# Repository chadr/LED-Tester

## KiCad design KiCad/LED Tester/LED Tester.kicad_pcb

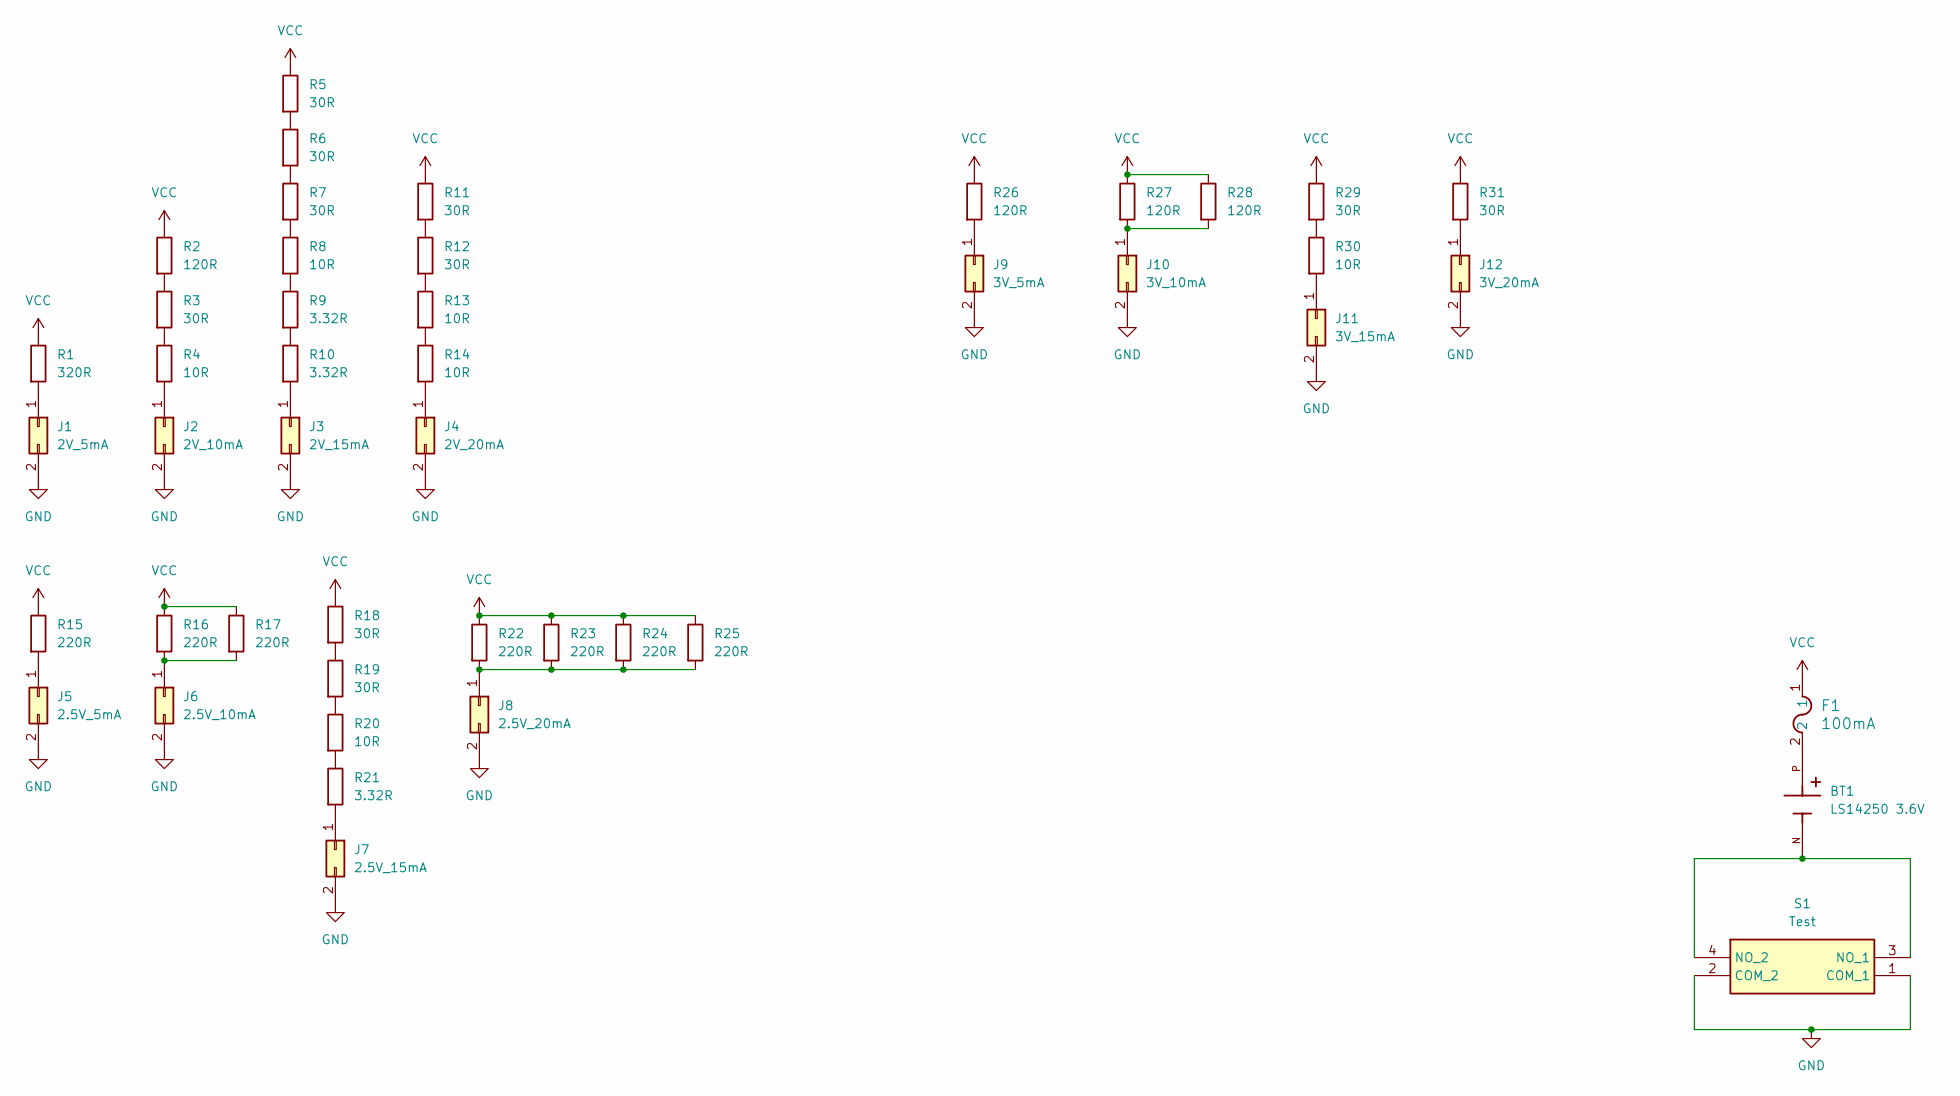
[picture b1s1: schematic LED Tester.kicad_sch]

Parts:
BT1: LS14250 3.6V; BAT_108; PARTREV E
F1: 100mA; FUSE_0PTF0078P_LTF
J1: 2V_5mA; PinHeader_2x01_P2.54mm_Vertical
J2: 2V_10mA; PinHeader_2x01_P2.54mm_Vertical
J3: 2V_15mA; PinHeader_2x01_P2.54mm_Vertical
J4: 2V_20mA; PinHeader_2x01_P2.54mm_Vertical
J5: 2.5V_5mA; PinHeader_2x01_P2.54mm_Vertical
J6: 2.5V_10mA; PinHeader_2x01_P2.54mm_Vertical
J7: 2.5V_15mA; PinHeader_2x01_P2.54mm_Vertical
J8: 2.5V_20mA; PinHeader_2x01_P2.54mm_Vertical
J9: 3V_5mA; PinHeader_2x01_P2.54mm_Vertical
J10: 3V_10mA; PinHeader_2x01_P2.54mm_Vertical
J11: 3V_15mA; PinHeader_2x01_P2.54mm_Vertical
J12: 3V_20mA; PinHeader_2x01_P2.54mm_Vertical
R1: 320R; R_1206_3216Metric
R2, R26, R27, R28: 120R; R_1206_3216Metric
R3, R5, R6, R7, R11, R12, R18, R19, R29, R31: 30R; R_1206_3216Metric
R4, R8, R13, R14, R20, R30: 10R; R_1206_3216Metric
R9, R10, R21: 3.32R; R_1206_3216Metric
R15, R16, R17, R22, R23, R24, R25: 220R; R_1206_3216Metric
S1: Test; FSM6JH; Manufacturer_Part_Number FSM6JH; Mouser Part Number 506-FSM6JH

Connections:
GND: J1.2, J2.2, J3.2, J4.2, J5.2, J6.2, J7.2, J8.2, J9.2, J10.2, J11.2, J12.2, S1.1 (COM_1), S1.2 (COM_2)
unnamed: BT1.P, F1.2
unnamed: J1.1, R1.2
unnamed: J2.1, R4.2
unnamed: J3.1, R10.2
unnamed: J4.1, R14.2
unnamed: J5.1, R15.2
unnamed: J6.1, R16.2, R17.2
unnamed: J7.1, R21.2
unnamed: J8.1, R22.2, R23.2, R24.2, R25.2
unnamed: J9.1, R26.2
unnamed: J10.1, R27.2, R28.2
unnamed: J11.1, R30.2
unnamed: J12.1, R31.2
unnamed: R2.2, R3.1
unnamed: R3.2, R4.1
unnamed: R5.2, R6.1
unnamed: R6.2, R7.1
unnamed: R7.2, R8.1
unnamed: R8.2, R9.1
unnamed: R9.2, R10.1
unnamed: R11.2, R12.1
unnamed: R12.2, R13.1
unnamed: R13.2, R14.1
unnamed: R18.2, R19.1
unnamed: R19.2, R20.1
unnamed: R20.2, R21.1
unnamed: R29.2, R30.1
unnamed: BT1.N, S1.3 (NO_1), S1.4 (NO_2)
VCC: F1.1, R1.1, R2.1, R5.1, R11.1, R15.1, R16.1, R17.1, R18.1, R22.1, R23.1, R24.1, R25.1, R26.1, R27.1, R28.1, R29.1, R31.1

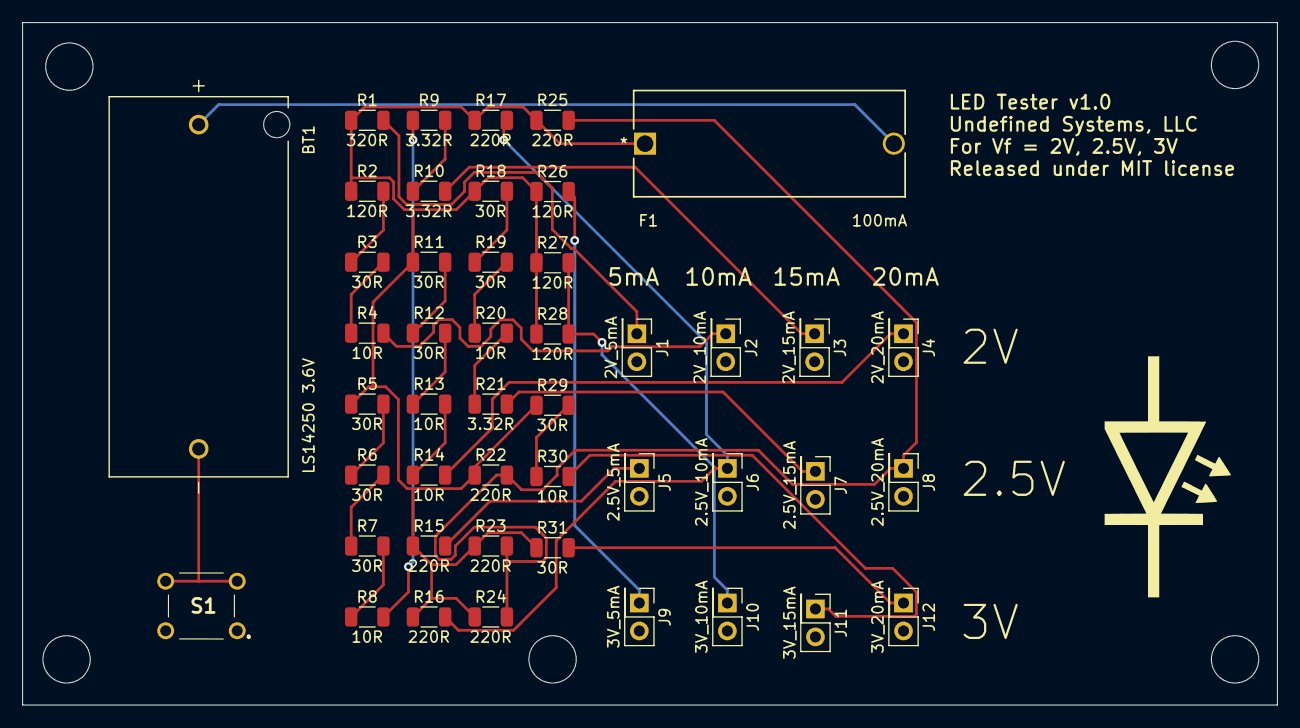
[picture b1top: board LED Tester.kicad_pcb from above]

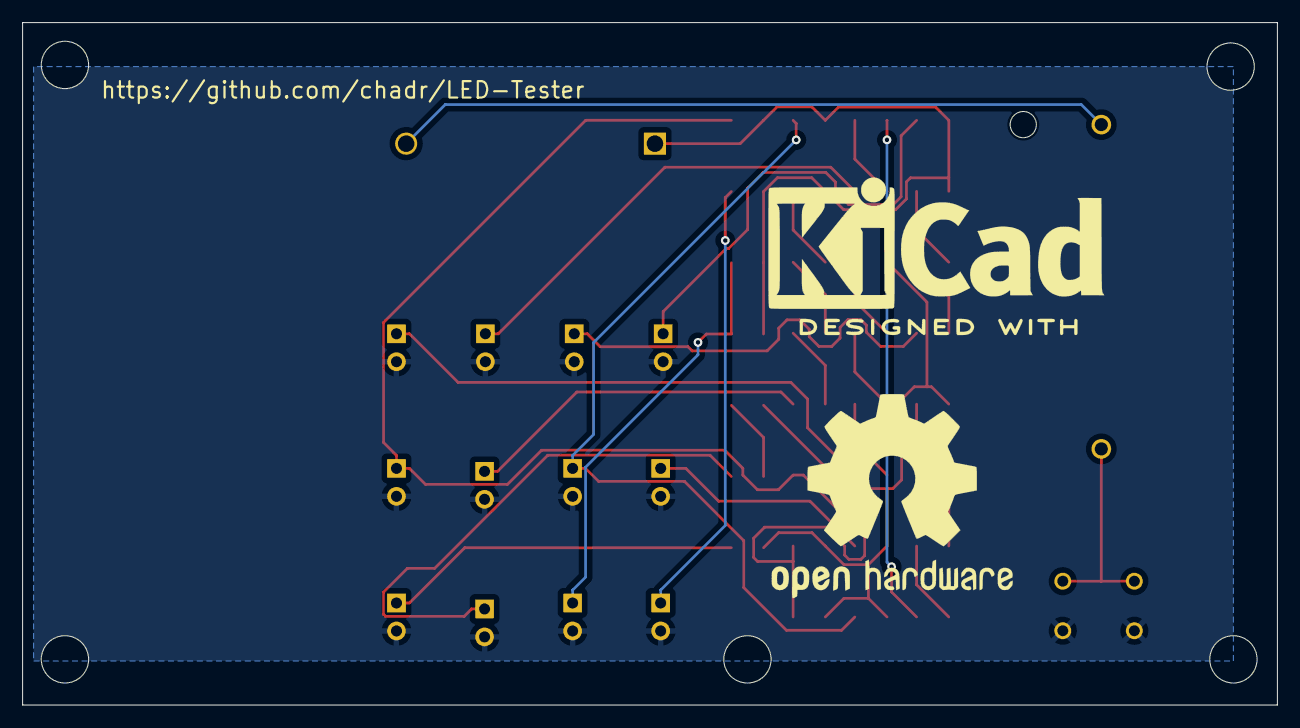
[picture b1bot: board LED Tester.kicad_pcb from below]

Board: 2 copper layers, 114.0 x 62.0 mm, 48 parts (2 on the bottom side), 30 nets.

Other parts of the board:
Logo1: KiCad-Logo2_12mm_SilkScreen
Logo2: OSHW-Logo2_24.3x20mm_SilkScreen

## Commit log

2023-12-26 update pcb size

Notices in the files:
KiCad/LED Tester/LED Tester.kicad_pcb:
Released under MIT license
